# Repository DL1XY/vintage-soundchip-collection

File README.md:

# Vintage Soundchip Collection

> Parts of this README were generated using AI.

My personal collection of vintage sound and speech chips from the 1970s to the early 1990s. Browse by part number for chip photos, datasheets, service manuals, and notes for building your own circuits. Each chip page also has a short story about where it showed up or what people got it to do.

## Circuit projects

- **UM6526P1 PAL TIA / ESP32 (Rev. A)**. Prototype design with structural checks. [Schematic PDF](CO10444_TIA/TIA_UM6526P1_Schematic_RevA_EN.pdf) · [Project files and verification notes](CO10444_TIA/TIA_UM6526P1_RevA_EN/README.md)
- **POKEY / ESP32 (Rev. A)**. Document-reviewed prototype design. [Schematic PDF](CO12294_POKEY/POKEY_ESP32_RevA_EN/POKEY_ESP32_Schematic_RevA_EN.pdf) · [Project files and verification notes](CO12294_POKEY/POKEY_ESP32_RevA_EN/README.md)

Both projects still need hardware testing.

## Chip catalog

| IC            | Company               | Type | Image         | KiCAD Symbol  |
| ------------- | --------------------- | ---- | ------------- | ------------- |
| [8245](8245)  | Intel                 | Multifunction (video/audio) |  | :triangular_ruler: |
| [AY-3-8910](AY-3-8910)  | General Instrument | PSG |  | :triangular_ruler: |
| [CDP1869](CDP1869) | RCA | Multifunction (video/audio) |  | :triangular_ruler: |
| [CO10444 TIA](CO10444_TIA) | Atari | Multifunction (video/audio) | <br>UM6526 TIA variant | :triangular_ruler: |
| [CO12294 POKEY](CO12294_POKEY) | Atari | Multifunction (I/O and audio) |  | :triangular_ruler: |
| [MEA8000](MEA8000) | TMPI | Speech synthesis |  | :triangular_ruler: |
| [MEB2636](MEB2636) | Signetics/Philips | Multifunction (video/audio) |  | :triangular_ruler: |
| [MM54104 DIGITALKER](MM54104) | Mozer| Speech synthesis |  | :triangular_ruler:  |
| [MN6221](MN6221) | Panasonic| Melody generator | <br>MN6221AA | :triangular_ruler:  |
| [MOS6560 VIC](MOS6560_VIC) | Commodore| Multifunction (video/audio) | <br>MOS6561 PAL VIC | :triangular_ruler: |
| [MOS6581 SID](MOS6581_SID) | Commodore| Subtractive synthesis |  | :triangular_ruler: |
| [MOS8360 TED](MOS8360_TED) | Commodore| Multifunction (video/audio) |  | :triangular_ruler: |
| [MOS8364 PAULA](MOS8364_PAULA) | Commodore| Multifunction (PCM audio and I/O) |  | :triangular_ruler: |
| [MSM5205](MSM5205) | OKI| ADPCM | <br>M5205 | :triangular_ruler:  |
| [MSM5218](MSM5218) | OKI| ADPCM | <br>M5218 | :triangular_ruler:  |
| [PCF8200](PCF8200) | Philips| Speech synthesis |  | :triangular_ruler:  |
| [SC-01](SC-01) | Votrax| Speech synthesis | <br>SC-01-A | No symbol |
| [SAA1099](SAA1099) | Philips| PSG |  | :triangular_ruler: |
| [SN76477](SN76477) | Texas Instruments| Sound effects generator |  | :triangular_ruler: |
| [SN76488](SN76488) | Texas Instruments| Sound effects generator |  | :triangular_ruler: |
| [SN76489](SN76489) | Texas Instruments| PSG | <br>SN76489AN | :triangular_ruler: |
| [SP0250](SP0250) | General Instrument| Speech synthesis |  | :triangular_ruler: |
| [SP0256](SP0256) | General Instrument| Speech synthesis | <br>SP0256A | :triangular_ruler: |
| [SP1000](SP1000) | General Instrument| Speech synthesis and recognition |  | :triangular_ruler: |
| [TMS3477](TMS3477) | Texas Instruments| Voice recording/playback |  | :triangular_ruler: |
| [TMS5110](TMS5110) | Texas Instruments| Speech synthesis |  | :triangular_ruler: |
| [TMS5200](TMS5200) | Texas Instruments| Speech synthesis |  | :triangular_ruler: |
| [TMS5220](TMS5220) | Texas Instruments| Speech synthesis |  | :triangular_ruler: |
| [UAA1003](UAA1003) | ITT| Speech synthesis |  | :triangular_ruler: |
| [VRC6](VRC6) | Konami| Multifunction (mapper/audio) | No image |No symbol |
| [VLM5030](VLM5030) | Sanyo| Speech synthesis |  | :triangular_ruler: |
| [YM2151](YM2151) | Yamaha| FM synthesis |  | :triangular_ruler: |
| [YM2203](YM2203) | Yamaha| FM synthesis + PSG |  | :triangular_ruler: |
| [YM2413](YM2413) | Yamaha| FM synthesis |  | :triangular_ruler: |
| [YM2610](YM2610) | Yamaha| FM synthesis + PSG + ADPCM |  | :triangular_ruler: |
| [YM3438](YM3438) | Yamaha| FM synthesis |  | :triangular_ruler: |
| [YM3812](YM3812) | Yamaha| FM synthesis |  | :triangular_ruler: |

PSG = programmable sound generator. Multifunction chips provide audio alongside other hardware functions.

## KiCAD Symbols

[8_bit_soundchips.kicad_sym](8_bit_soundchips.kicad_sym) contains KiCAD symbols of chips marked with :triangular_ruler:

Tested with KiCAD 10.x

## Wishlist

+ Ricoh 2A03/2A07
+ Sunsoft 5B
+ misc Harris 
+ misc Nintendo (MMC5, 2C33, ...)
+ misc Yamaha
+ misc Konami (RC,...)
+ misc Namco (WSG, 163, ...)
+ OKI MSM5232
+ OKI 6295

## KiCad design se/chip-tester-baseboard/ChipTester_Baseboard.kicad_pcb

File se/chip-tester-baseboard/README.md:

# USB-C Sound Chip Tester Baseboard · Rev A

Open [ChipTester_Baseboard.kicad_pro](ChipTester_Baseboard.kicad_pro) in KiCad 8 or newer. The project has five schematic sheets and an 82 × 69 mm four-layer PCB. Keep the schematic sheets, library tables, symbol library and `Baseboard.pretty` folder together. The PCB includes routed copper and an In1.Cu ground zone. Press **B** in the PCB Editor to fill the zone before running DRC.

| Sheet | Circuit |
| --- | --- |
| USB-C | GCT USB4105 receptacle, separate CC pull-downs, flow-through USBLC6 data ESD clamp and 27 Ω series resistors |
| Power | AP2112K 3.3 V supply and firmware-enabled TPS2553 adapter supply. Pull-down on the enable input defaults the adapter supply off. |
| RP2350B | QSPI flash, 12 MHz crystal, 1.1 V core buck, BOOTSEL, reset and SWD |
| Adapter | One keyed 2×20 IDC connector with the pin numbering from the [architecture](../chip-tester-design.md). Disconnect USB to swap adapters. |
| Audio | Independent, AC-coupled L/MONO and R line outputs. Fixed unity-gain buffers and default mute. Use line inputs of 10 kΩ or higher. |

The layout uses an internal ground plane and places the audio buffers, analog switch and filter components next to the output jacks. Two buffered controls drive the analog switch at its 5 V logic levels. The adapter supplies the chip-specific signal conditioning and output level. A mono adapter connects to `AUDIO_L`. Leave the right channel muted in firmware.

## RP2350B firmware pin assignments

| GPIO | Signal |
| --- | --- |
| GP4–GP11 | D0–D7, contiguous for PIO |
| GP12–GP17 | A0–A5 |
| GP18–GP21 | CTRL0–CTRL3 |
| GP22, GP23 | CLK_OUT, RESET_N |
| GP24, GP25 | ID_SDA, ID_SCL |
| GP26, GP27 | BUS_EN, DATA_DIR |
| GP28, GP29–GP31 | READY_IRQ, AUX0–AUX2 |
| GP32, GP33 | ADAPTER_EN, ADAPTER_FAULT_N |
| GP34, GP35 | AUDIO_L_EN, AUDIO_R_EN |

Adapter ID runs on the always-on 3.3 V pin and dedicated ID bus. Keep the adapter's 5 V supply and bus drivers disabled through USB configuration and profile identification. On suspend or fault, mute the outputs, disable the bus and remove adapter power. This project contains the hardware. USB CDC commands and chip profiles require firmware.

## Prototype verification

The schematic and PCB were checked for footprint linkage, pin-to-net agreement and routed connectivity. KiCad ERC, filled-zone DRC and native import remain to be run. Before sending Gerbers, review the USB pair and chosen PCB stack-up, ground fill, component land patterns and fab limits. The layout uses 0.40 mm signal vias with 0.20 mm finished drills and 0.12 mm minimum design clearance. The RP2350B exposed pad requires reflow assembly. Review stencil apertures and exposed-pad via treatment with the board supplier.

On initial power-up, measure protected VBUS, 3.3 V, 1.1 V and the audio midpoint. Check USB enumeration and BOOTSEL with the adapter supply off, then verify the TPS2553 current limit with a dummy load. The 82.5 kΩ limit resistor is provisional pending measurements of baseboard current, adapter inrush and total USB current. Measure audio noise, output level and power-transition transients before using the line outputs for comparisons.

The [batch workbook](../chip-tester-bom/Chip%20Tester%20BOM.xlsx) is the earlier cost estimate. Extract the baseboard purchase list from the schematic. This revision adds an SN74AHCT125 buffer and uses 0402 passives near the RP2350B and analog switch.

## Design references

- [Raspberry Pi RP2350 hardware design guide](https://pip-assets.raspberrypi.com/categories/1214-rp2350/documents/RP-008280-DS-1-hardware-design-with-rp2350.pdf)
- [GCT USB4105 mechanical drawing](https://gct.co/files/drawings/usb4105.pdf)
- [ST USBLC6-2SC6 datasheet](https://www.st.com/resource/en/datasheet/usblc6-2sc6.pdf)
- [TI TPS2553 datasheet](https://www.ti.com/lit/ds/symlink/tps2553.pdf)
- [TI TS5A23157 datasheet](https://www.ti.com/lit/ds/symlink/ts5a23157.pdf)
- [Same Sky SJ1-3523N mechanical drawing](https://www.sameskydevices.com/product/resource/sj1-352xn.pdf)

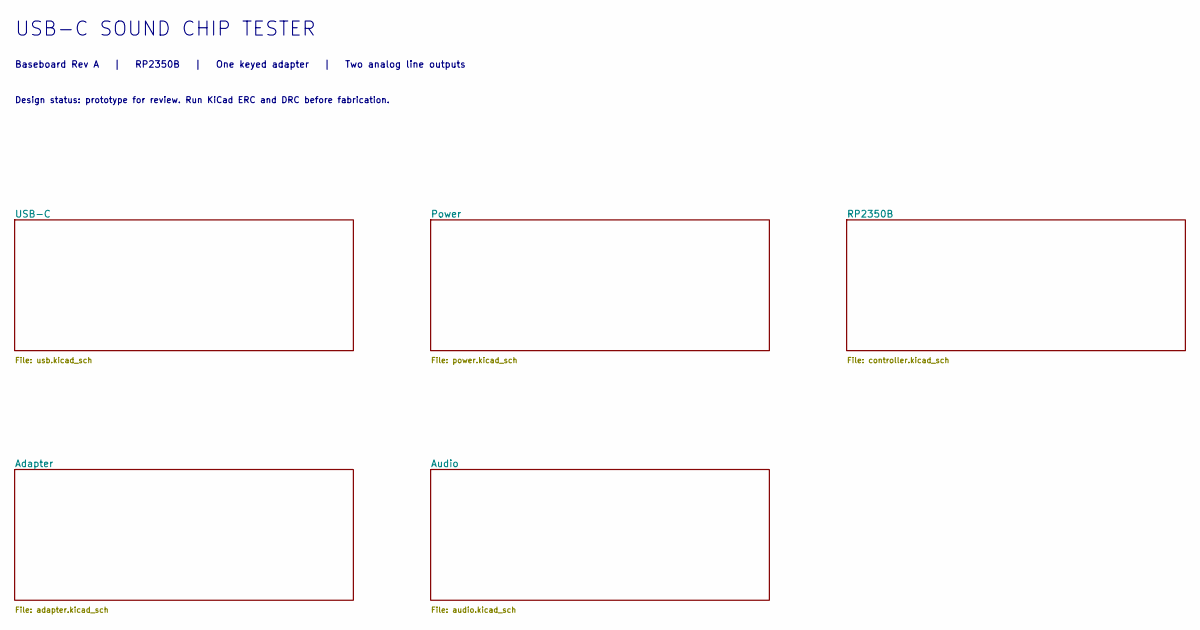
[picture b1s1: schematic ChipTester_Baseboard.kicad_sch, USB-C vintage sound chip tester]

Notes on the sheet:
USB-C SOUND CHIP TESTER
Design status: prototype for review. Run KiCad ERC and DRC before fabrication.
Baseboard Rev A | RP2350B | One keyed adapter | Two analog line outputs

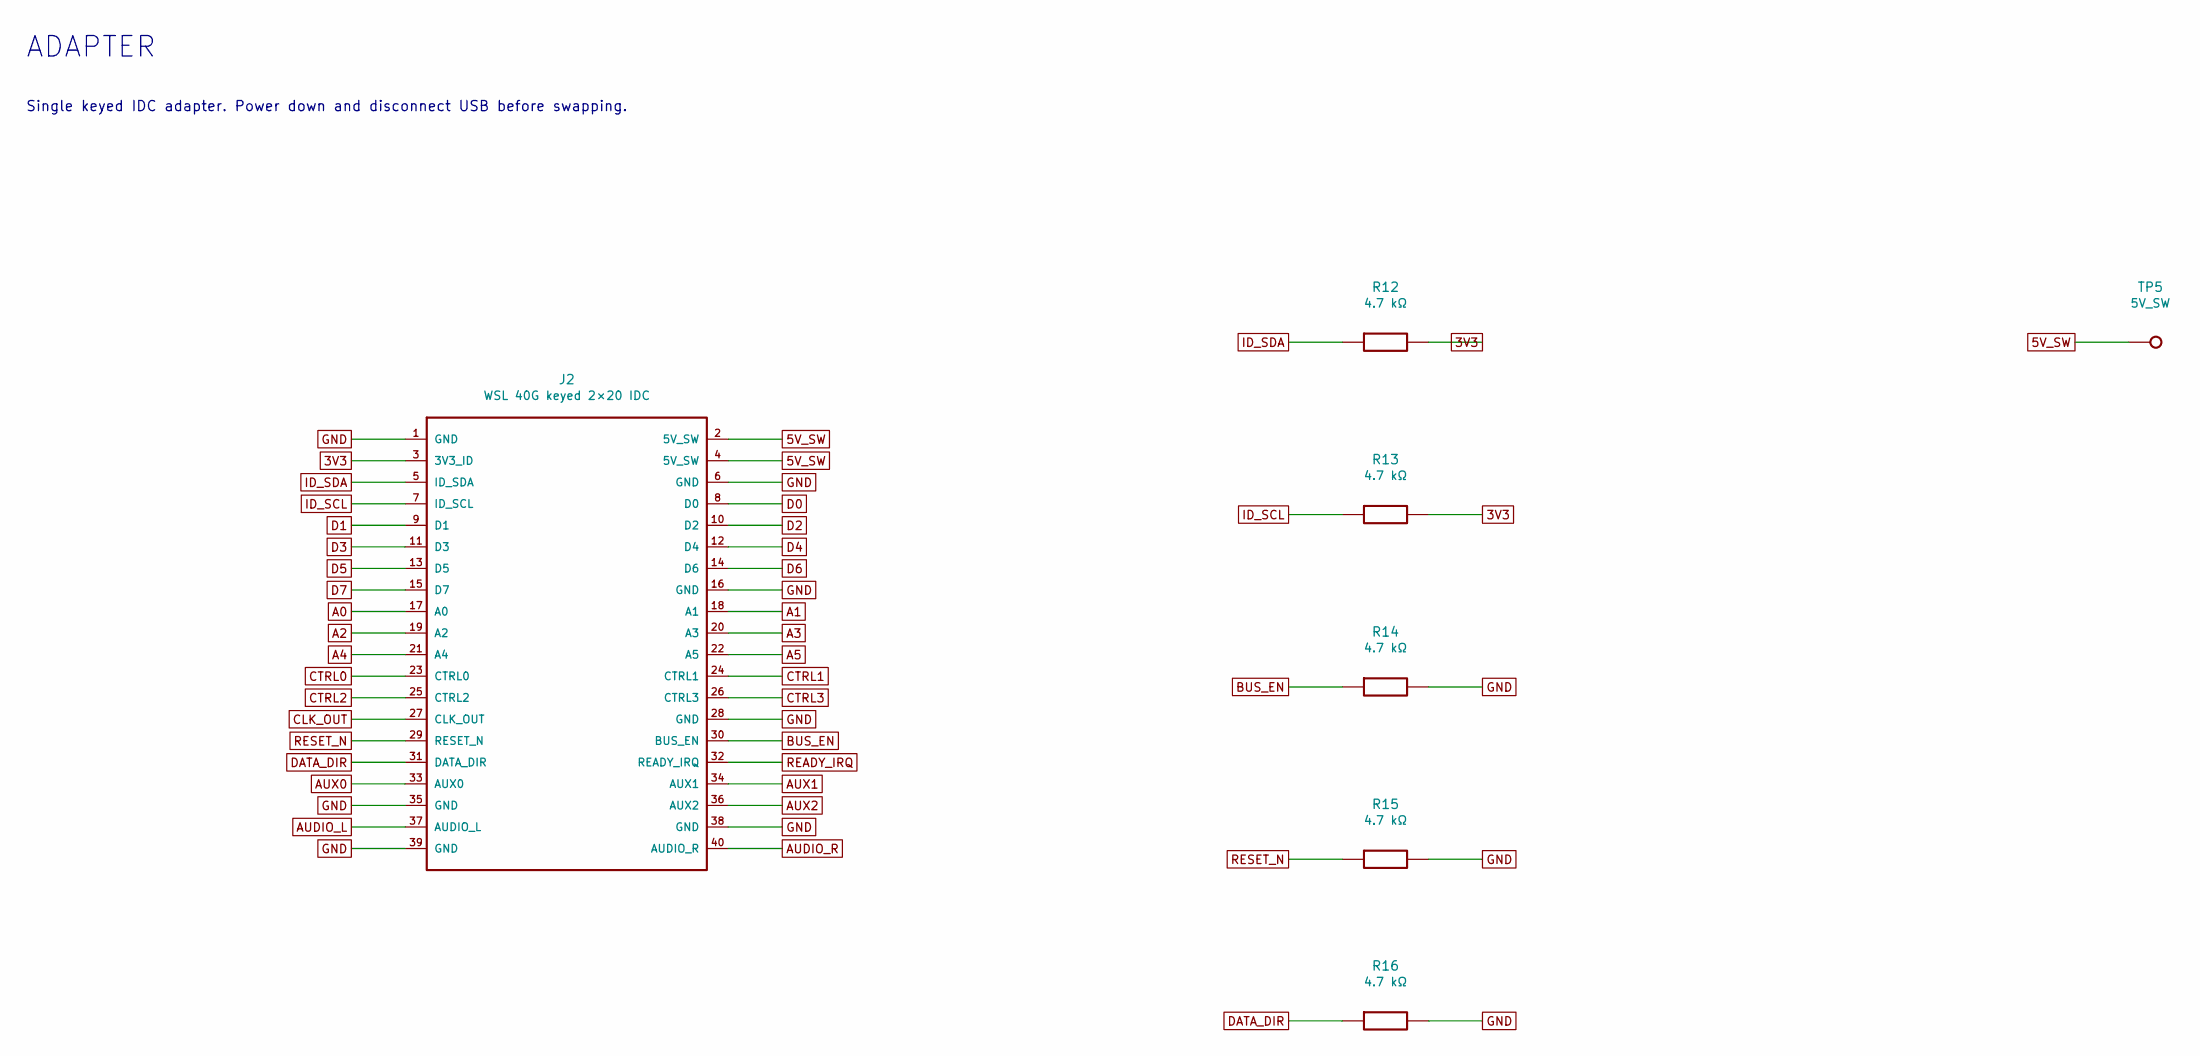
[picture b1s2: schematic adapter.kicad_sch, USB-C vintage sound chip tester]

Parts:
J2: WSL 40G keyed 2×20 IDC; IDC_2x20
R12, R13, R14, R15, R16: 4.7 kΩ; R_0805
TP5: 5V_SW; TestPoint_1mm

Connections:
3V3: J2.3 (3V3_ID), R12.2, R13.2; also elsewhere on the board
5V_SW: J2.2 (5V_SW), J2.4 (5V_SW), TP5.1; also elsewhere on the board
A0: J2.17 (A0); also elsewhere on the board
A1: J2.18 (A1); also elsewhere on the board
A2: J2.19 (A2); also elsewhere on the board
A3: J2.20 (A3); also elsewhere on the board
A4: J2.21 (A4); also elsewhere on the board
A5: J2.22 (A5); also elsewhere on the board
AUDIO_L: J2.37 (AUDIO_L); also elsewhere on the board
AUDIO_R: J2.40 (AUDIO_R); also elsewhere on the board
AUX0: J2.33 (AUX0); also elsewhere on the board
AUX1: J2.34 (AUX1); also elsewhere on the board
AUX2: J2.36 (AUX2); also elsewhere on the board
BUS_EN: J2.30 (BUS_EN), R14.1; also elsewhere on the board
CLK_OUT: J2.27 (CLK_OUT); also elsewhere on the board
CTRL0: J2.23 (CTRL0); also elsewhere on the board
CTRL1: J2.24 (CTRL1); also elsewhere on the board
CTRL2: J2.25 (CTRL2); also elsewhere on the board
CTRL3: J2.26 (CTRL3); also elsewhere on the board
D0: J2.8 (D0); also elsewhere on the board
D1: J2.9 (D1); also elsewhere on the board
D2: J2.10 (D2); also elsewhere on the board
D3: J2.11 (D3); also elsewhere on the board
D4: J2.12 (D4); also elsewhere on the board
D5: J2.13 (D5); also elsewhere on the board
D6: J2.14 (D6); also elsewhere on the board
D7: J2.15 (D7); also elsewhere on the board
DATA_DIR: J2.31 (DATA_DIR), R16.1; also elsewhere on the board
GND: J2.1 (GND), J2.6 (GND), J2.16 (GND), J2.28 (GND), J2.35 (GND), J2.38 (GND), J2.39 (GND), R14.2, R15.2, R16.2; also elsewhere on the board
ID_SCL: J2.7 (ID_SCL), R13.1; also elsewhere on the board
ID_SDA: J2.5 (ID_SDA), R12.1; also elsewhere on the board
READY_IRQ: J2.32 (READY_IRQ); also elsewhere on the board
RESET_N: J2.29 (RESET_N), R15.1; also elsewhere on the board

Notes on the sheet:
ADAPTER
Single keyed IDC adapter. Power down and disconnect USB before swapping.

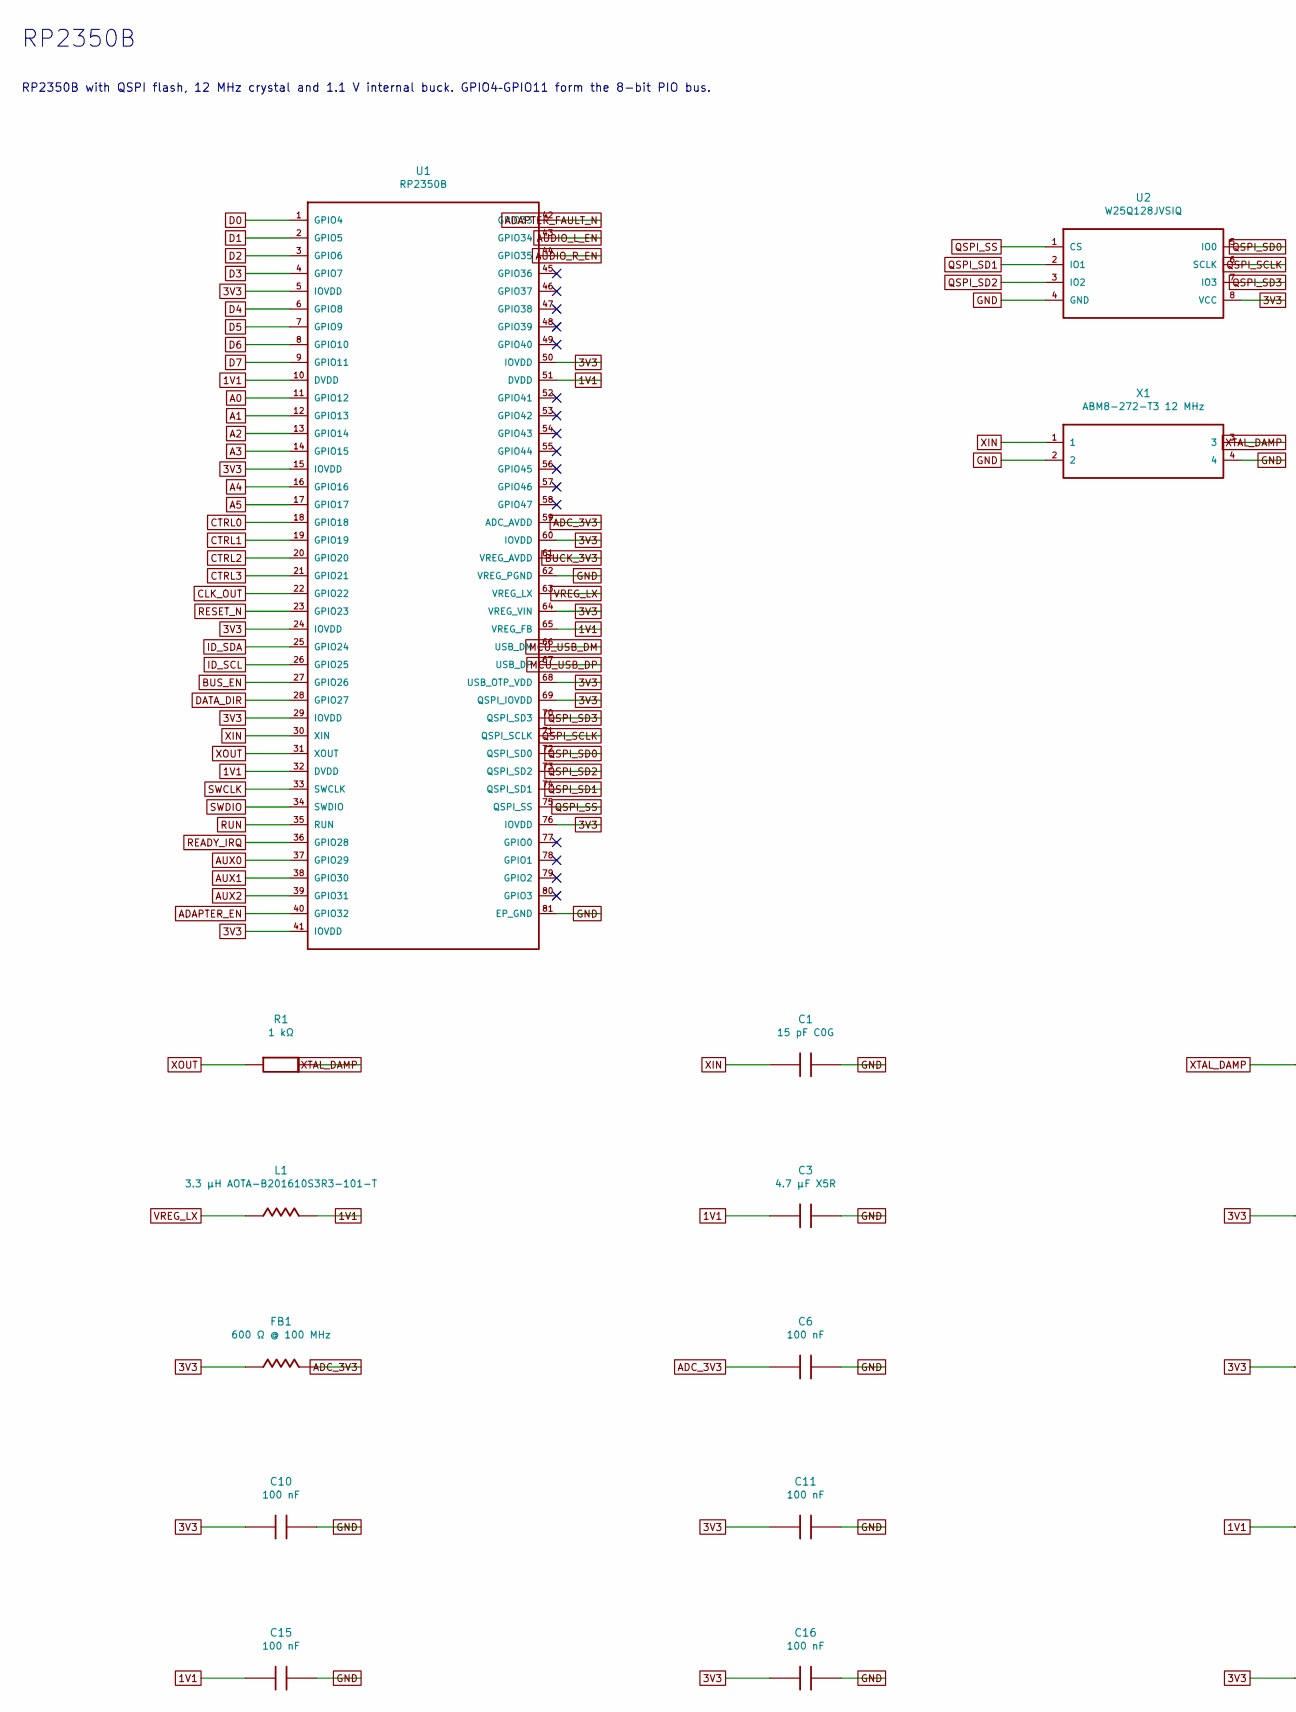
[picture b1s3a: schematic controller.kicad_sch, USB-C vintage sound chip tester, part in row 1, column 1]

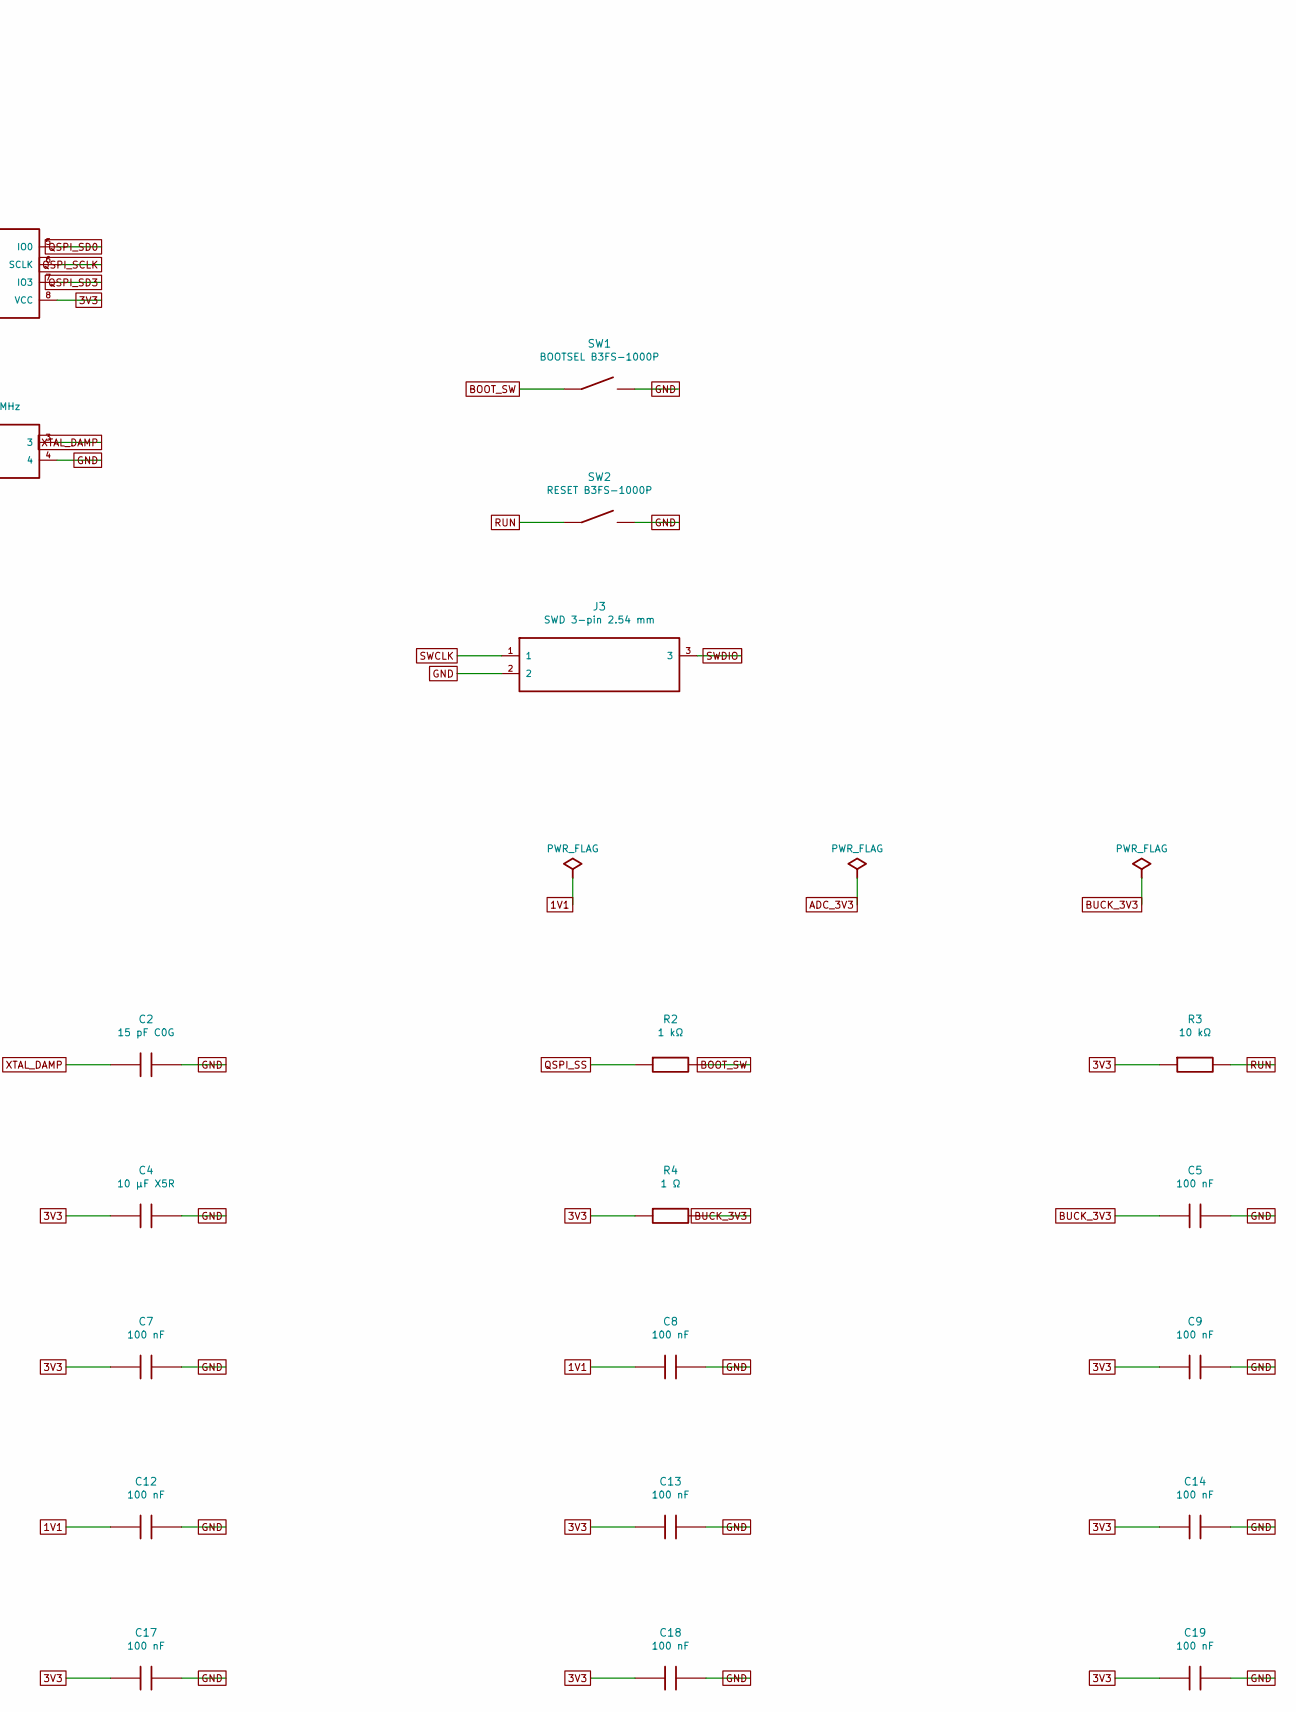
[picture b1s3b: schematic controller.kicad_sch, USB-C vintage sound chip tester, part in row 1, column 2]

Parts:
C1, C2: 15 pF C0G; C_0402
C3: 4.7 µF X5R; C_0603
C4: 10 µF X5R; C_0603_R90
C5, C6, C7, C8, C9, C11, C12, C13, C14, C15, C16, C18, C19: 100 nF; C_0402
C10, C17: 100 nF; C_0402_R90
FB1: 600 Ω @ 100 MHz; FB_0603
J3: SWD 3-pin 2.54 mm; Header_1x03
L1: 3.3 µH AOTA-B201610S3R3-101-T; L_L2016
R1, R2: 1 kΩ; R_0402
R3: 10 kΩ; R_0805
R4: 1 Ω; R_0402
SW1: BOOTSEL B3FS-1000P; B3FS_1000P
SW2: RESET B3FS-1000P; B3FS_1000P
U1: RP2350B; QFN80_RP2350B
U2: W25Q128JVSIQ; SOIC8_5.3mm_R90
X1: ABM8-272-T3 12 MHz; Crystal_3225

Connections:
1V1: C3.1, C8.1, C12.1, C15.1, L1.2, U1.10 (DVDD), U1.32 (DVDD), U1.51 (DVDD), U1.65 (VREG_FB); also elsewhere on the board
3V3: C4.1, C7.1, C9.1, C10.1, C11.1, C13.1, C14.1, C16.1, C17.1, C18.1, C19.1, FB1.1, R3.1, R4.1, U1.5 (IOVDD), U1.15 (IOVDD), U1.24 (IOVDD), U1.29 (IOVDD), U1.41 (IOVDD), U1.50 (IOVDD), U1.60 (IOVDD), U1.64 (VREG_VIN), U1.68 (USB_OTP_VDD), U1.69 (QSPI_IOVDD), U1.76 (IOVDD), U2.8 (VCC); also elsewhere on the board
A0: U1.11 (GPIO12); also elsewhere on the board
A1: U1.12 (GPIO13); also elsewhere on the board
A2: U1.13 (GPIO14); also elsewhere on the board
A3: U1.14 (GPIO15); also elsewhere on the board
A4: U1.16 (GPIO16); also elsewhere on the board
A5: U1.17 (GPIO17); also elsewhere on the board
ADAPTER_EN: U1.40 (GPIO32); also elsewhere on the board
ADAPTER_FAULT_N: U1.42 (GPIO33); also elsewhere on the board
ADC_3V3: C6.1, FB1.2, U1.59 (ADC_AVDD)
AUDIO_L_EN: U1.43 (GPIO34); also elsewhere on the board
AUDIO_R_EN: U1.44 (GPIO35); also elsewhere on the board
AUX0: U1.37 (GPIO29); also elsewhere on the board
AUX1: U1.38 (GPIO30); also elsewhere on the board
AUX2: U1.39 (GPIO31); also elsewhere on the board
BOOT_SW: R2.2, SW1.1
BUCK_3V3: C5.1, R4.2, U1.61 (VREG_AVDD)
BUS_EN: U1.27 (GPIO26); also elsewhere on the board
CLK_OUT: U1.22 (GPIO22); also elsewhere on the board
CTRL0: U1.18 (GPIO18); also elsewhere on the board
CTRL1: U1.19 (GPIO19); also elsewhere on the board
CTRL2: U1.20 (GPIO20); also elsewhere on the board
CTRL3: U1.21 (GPIO21); also elsewhere on the board
D0: U1.1 (GPIO4); also elsewhere on the board
D1: U1.2 (GPIO5); also elsewhere on the board
D2: U1.3 (GPIO6); also elsewhere on the board
D3: U1.4 (GPIO7); also elsewhere on the board
D4: U1.6 (GPIO8); also elsewhere on the board
D5: U1.7 (GPIO9); also elsewhere on the board
D6: U1.8 (GPIO10); also elsewhere on the board
D7: U1.9 (GPIO11); also elsewhere on the board
DATA_DIR: U1.28 (GPIO27); also elsewhere on the board
GND: C1.2, C2.2, C3.2, C4.2, C5.2, C6.2, C7.2, C8.2, C9.2, C10.2, C11.2, C12.2, C13.2, C14.2, C15.2, C16.2, C17.2, C18.2, C19.2, J3.2, SW1.2, SW2.2, U1.62 (VREG_PGND), U1.81 (EP_GND), U2.4 (GND), X1.2, X1.4; also elsewhere on the board
ID_SCL: U1.26 (GPIO25); also elsewhere on the board
ID_SDA: U1.25 (GPIO24); also elsewhere on the board
MCU_USB_DM: U1.66 (USB_DM); also elsewhere on the board
MCU_USB_DP: U1.67 (USB_DP); also elsewhere on the board
QSPI_SCLK: U1.71 (QSPI_SCLK), U2.6 (SCLK)
QSPI_SD0: U1.72 (QSPI_SD0), U2.5 (IO0)
QSPI_SD1: U1.74 (QSPI_SD1), U2.2 (IO1)
QSPI_SD2: U1.73 (QSPI_SD2), U2.3 (IO2)
QSPI_SD3: U1.70 (QSPI_SD3), U2.7 (IO3)
QSPI_SS: R2.1, U1.75 (QSPI_SS), U2.1 (CS)
READY_IRQ: U1.36 (GPIO28); also elsewhere on the board
RESET_N: U1.23 (GPIO23); also elsewhere on the board
RUN: R3.2, SW2.1, U1.35 (RUN)
SWCLK: J3.1, U1.33 (SWCLK)
SWDIO: J3.3, U1.34 (SWDIO)
VREG_LX: L1.1, U1.63 (VREG_LX)
XIN: C1.1, U1.30 (XIN), X1.1
XOUT: R1.1, U1.31 (XOUT)
XTAL_DAMP: C2.1, R1.2, X1.3

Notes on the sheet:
RP2350B with QSPI flash, 12 MHz crystal and 1.1 V internal buck. GPIO4–GPIO11 form the 8-bit PIO bus.
RP2350B

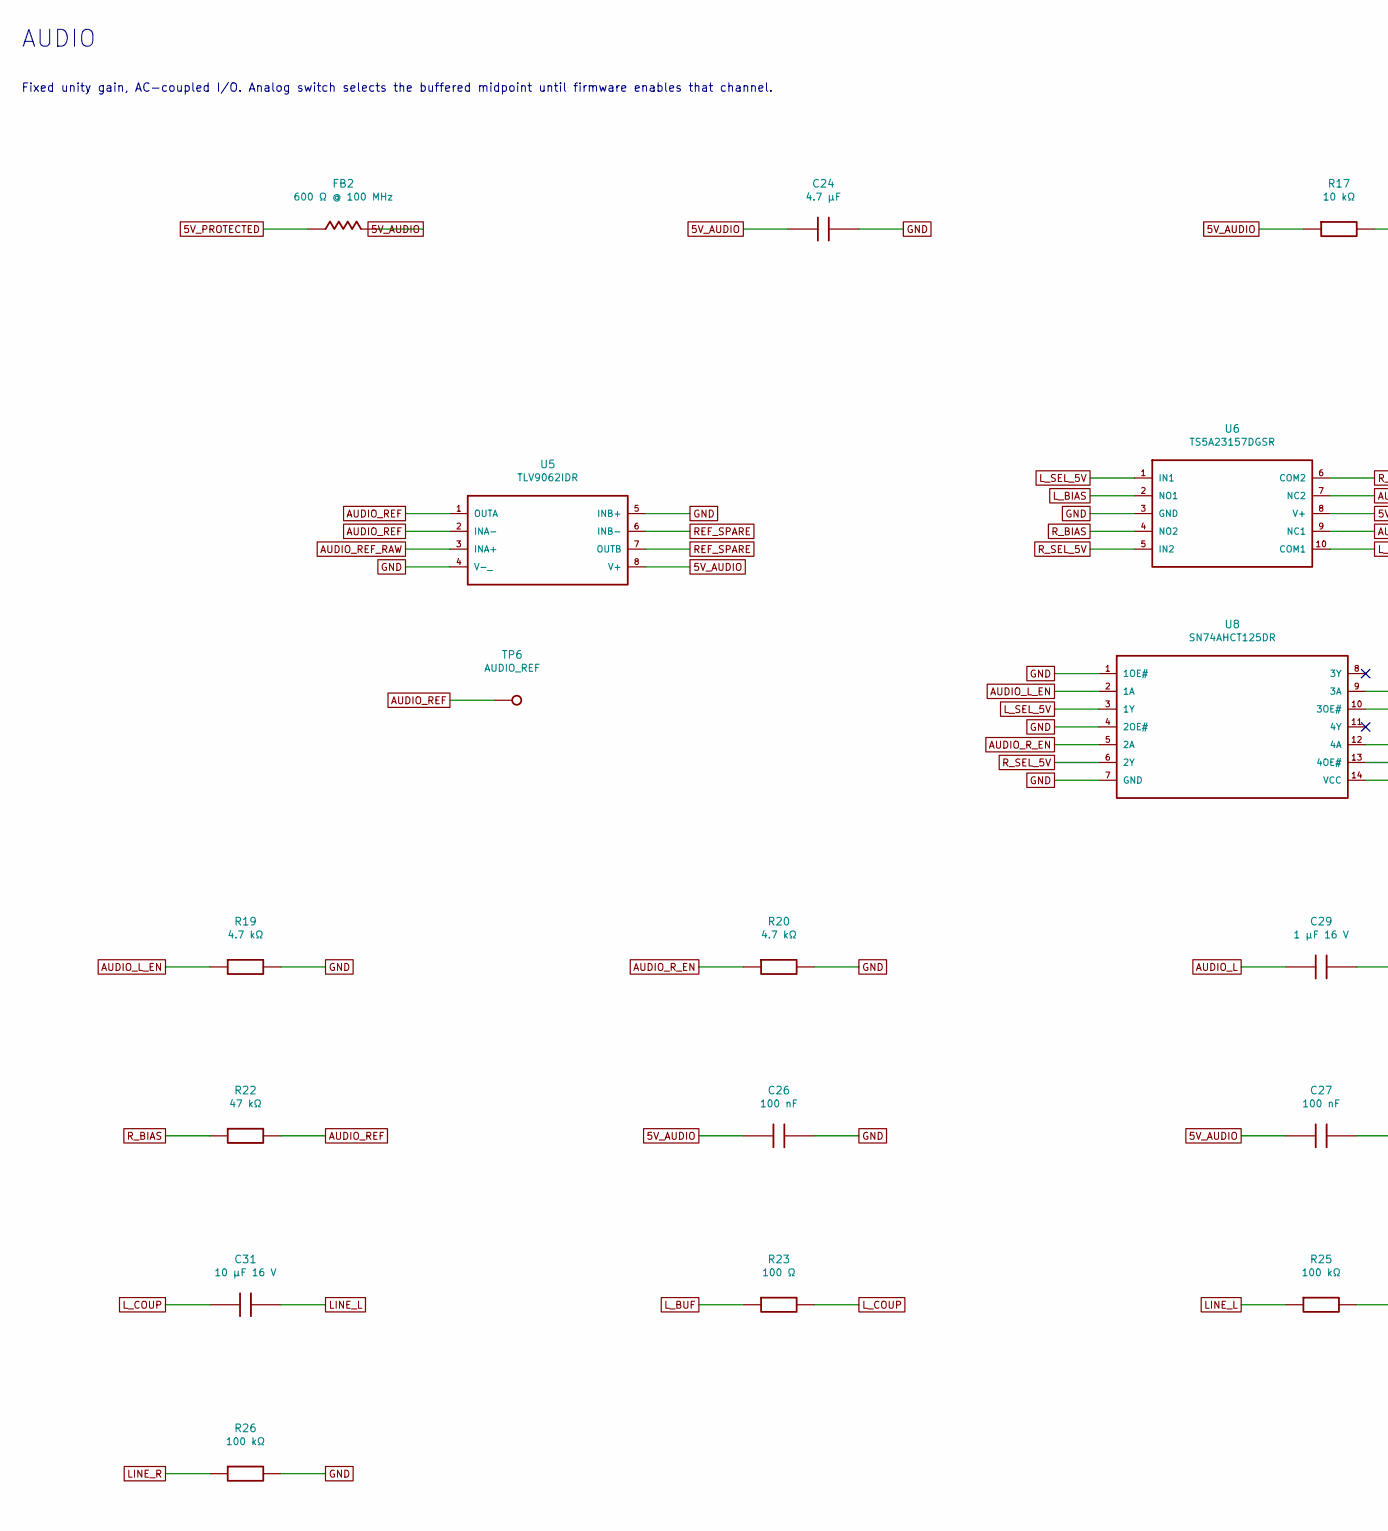
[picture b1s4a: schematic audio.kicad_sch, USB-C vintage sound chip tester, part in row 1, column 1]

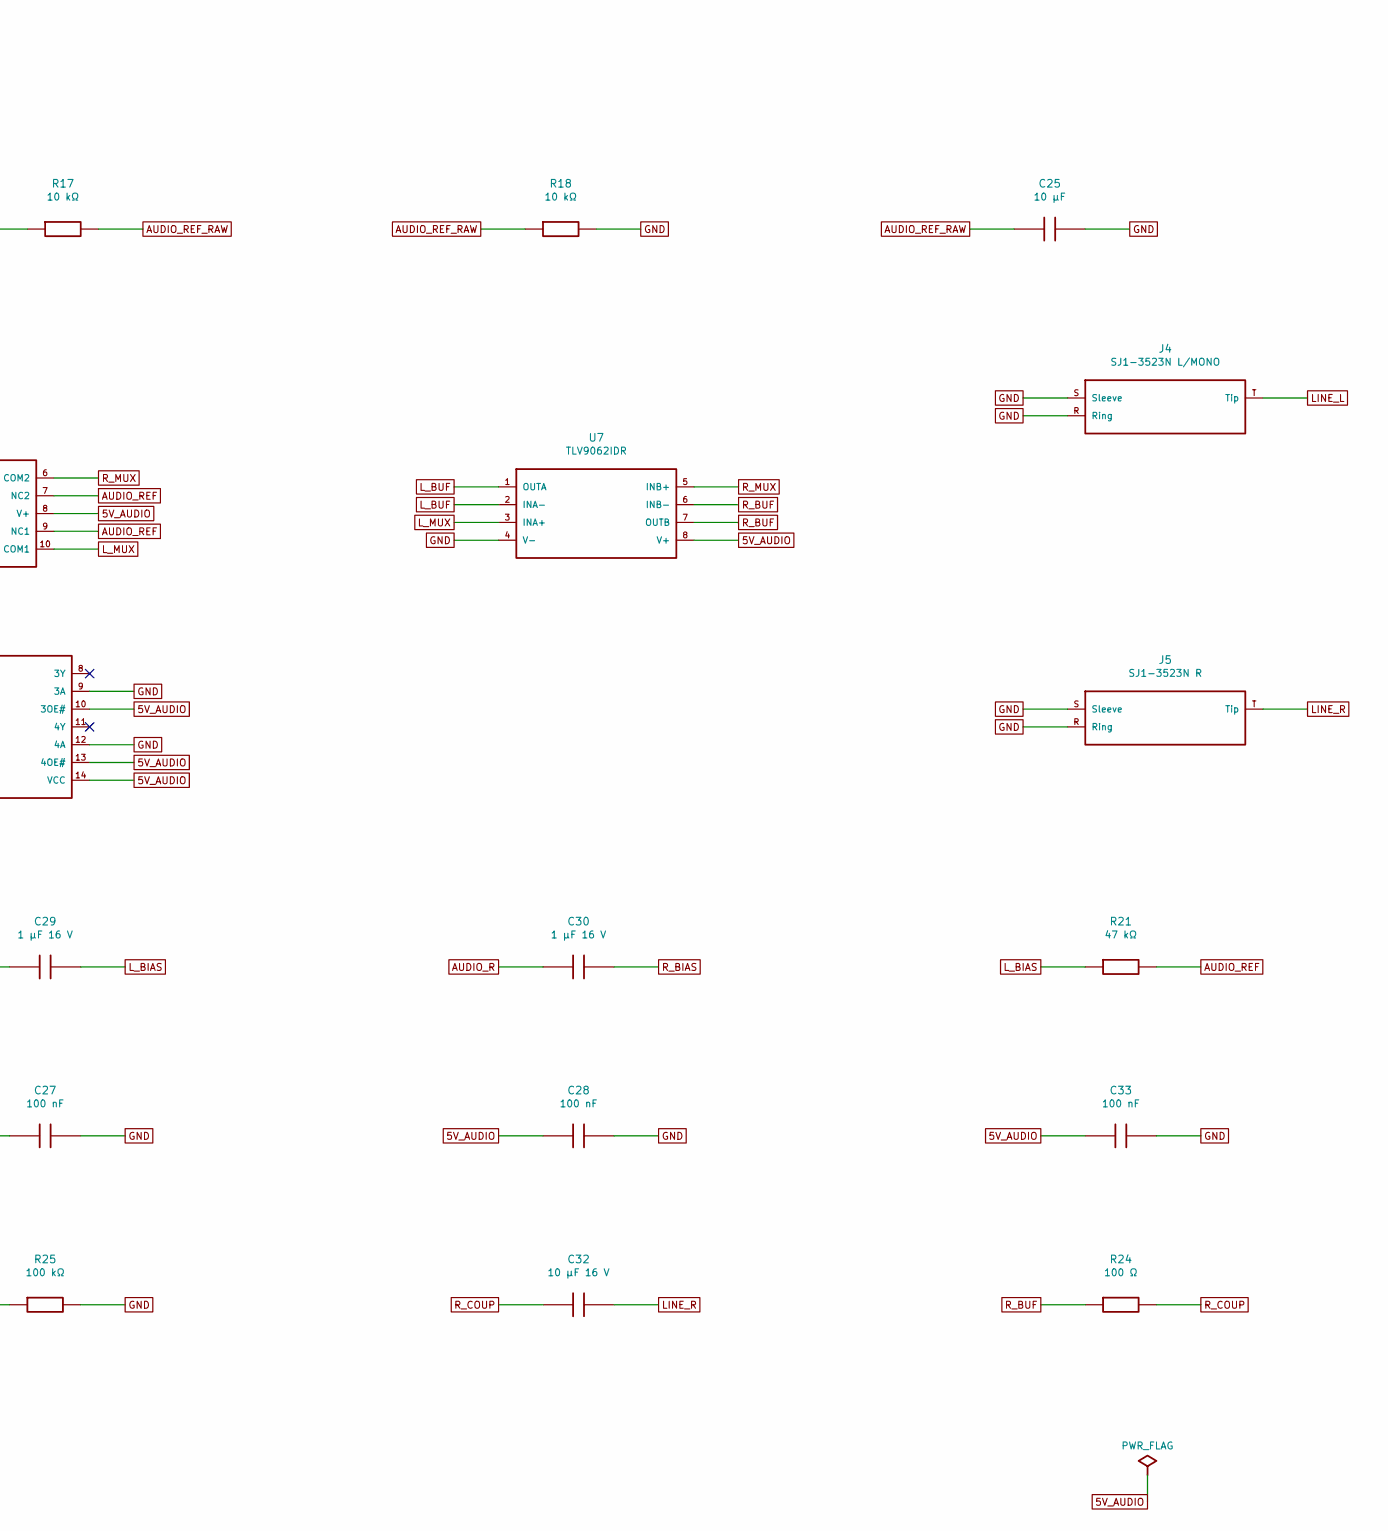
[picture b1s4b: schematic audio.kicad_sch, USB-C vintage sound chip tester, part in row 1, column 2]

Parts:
C24: 4.7 µF; C_0805
C25: 10 µF; C_0805
C26, C27, C28, C33: 100 nF; C_0402
C29, C30: 1 µF 16 V; C_0603_R90
C31, C32: 10 µF 16 V; C_1206
FB2: 600 Ω @ 100 MHz; FB_0805
J4: SJ1-3523N L/MONO; SJ1_3523N
J5: SJ1-3523N R; SJ1_3523N
R17, R18: 10 kΩ; R_0805
R19, R20: 4.7 kΩ; R_0603
R21, R22: 47 kΩ; R_0603_R90
R23: 100 Ω; R_0805
R24: 100 Ω; R_0805_R90
R25, R26: 100 kΩ; R_0603
TP6: AUDIO_REF; TestPoint_1mm
U5, U7: TLV9062IDR; SOIC8
U6: TS5A23157DGSR; VSSOP10
U8: SN74AHCT125DR; SOIC14

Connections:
5V_AUDIO: C24.1, C26.1, C27.1, C28.1, C33.1, FB2.2, R17.1, U5.8 (V+), U6.8 (V+), U7.8 (V+), U8.10 (3OE#), U8.13 (4OE#), U8.14 (VCC)
5V_PROTECTED: FB2.1; also elsewhere on the board
AUDIO_L: C29.1; also elsewhere on the board
AUDIO_L_EN: R19.1, U8.2 (1A); also elsewhere on the board
AUDIO_R: C30.1; also elsewhere on the board
AUDIO_REF: R21.2, R22.2, TP6.1, U5.1 (OUTA), U5.2 (INA-), U6.7 (NC2), U6.9 (NC1)
AUDIO_REF_RAW: C25.1, R17.2, R18.1, U5.3 (INA+)
AUDIO_R_EN: R20.1, U8.5 (2A); also elsewhere on the board
GND: C24.2, C25.2, C26.2, C27.2, C28.2, C33.2, J4.R (Ring), J4.S (Sleeve), J5.R (Ring), J5.S (Sleeve), R18.2, R19.2, R20.2, R25.2, R26.2, U5.4 (V-_), U5.5 (INB+), U6.3 (GND), U7.4 (V-), U8.1 (1OE#), U8.4 (2OE#), U8.7 (GND), U8.9 (3A), U8.12 (4A); also elsewhere on the board
LINE_L: C31.2, J4.T (Tip), R25.1
LINE_R: C32.2, J5.T (Tip), R26.1
L_BIAS: C29.2, R21.1, U6.2 (NO1)
L_BUF: R23.1, U7.1 (OUTA), U7.2 (INA-)
L_COUP: C31.1, R23.2
L_MUX: U6.10 (COM1), U7.3 (INA+)
L_SEL_5V: U6.1 (IN1), U8.3 (1Y)
REF_SPARE: U5.6 (INB-), U5.7 (OUTB)
R_BIAS: C30.2, R22.1, U6.4 (NO2)
R_BUF: R24.1, U7.6 (INB-), U7.7 (OUTB)
R_COUP: C32.1, R24.2
R_MUX: U6.6 (COM2), U7.5 (INB+)
R_SEL_5V: U6.5 (IN2), U8.6 (2Y)

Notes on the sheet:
AUDIO
Fixed unity gain, AC-coupled I/O. Analog switch selects the buffered midpoint until firmware enables that channel.

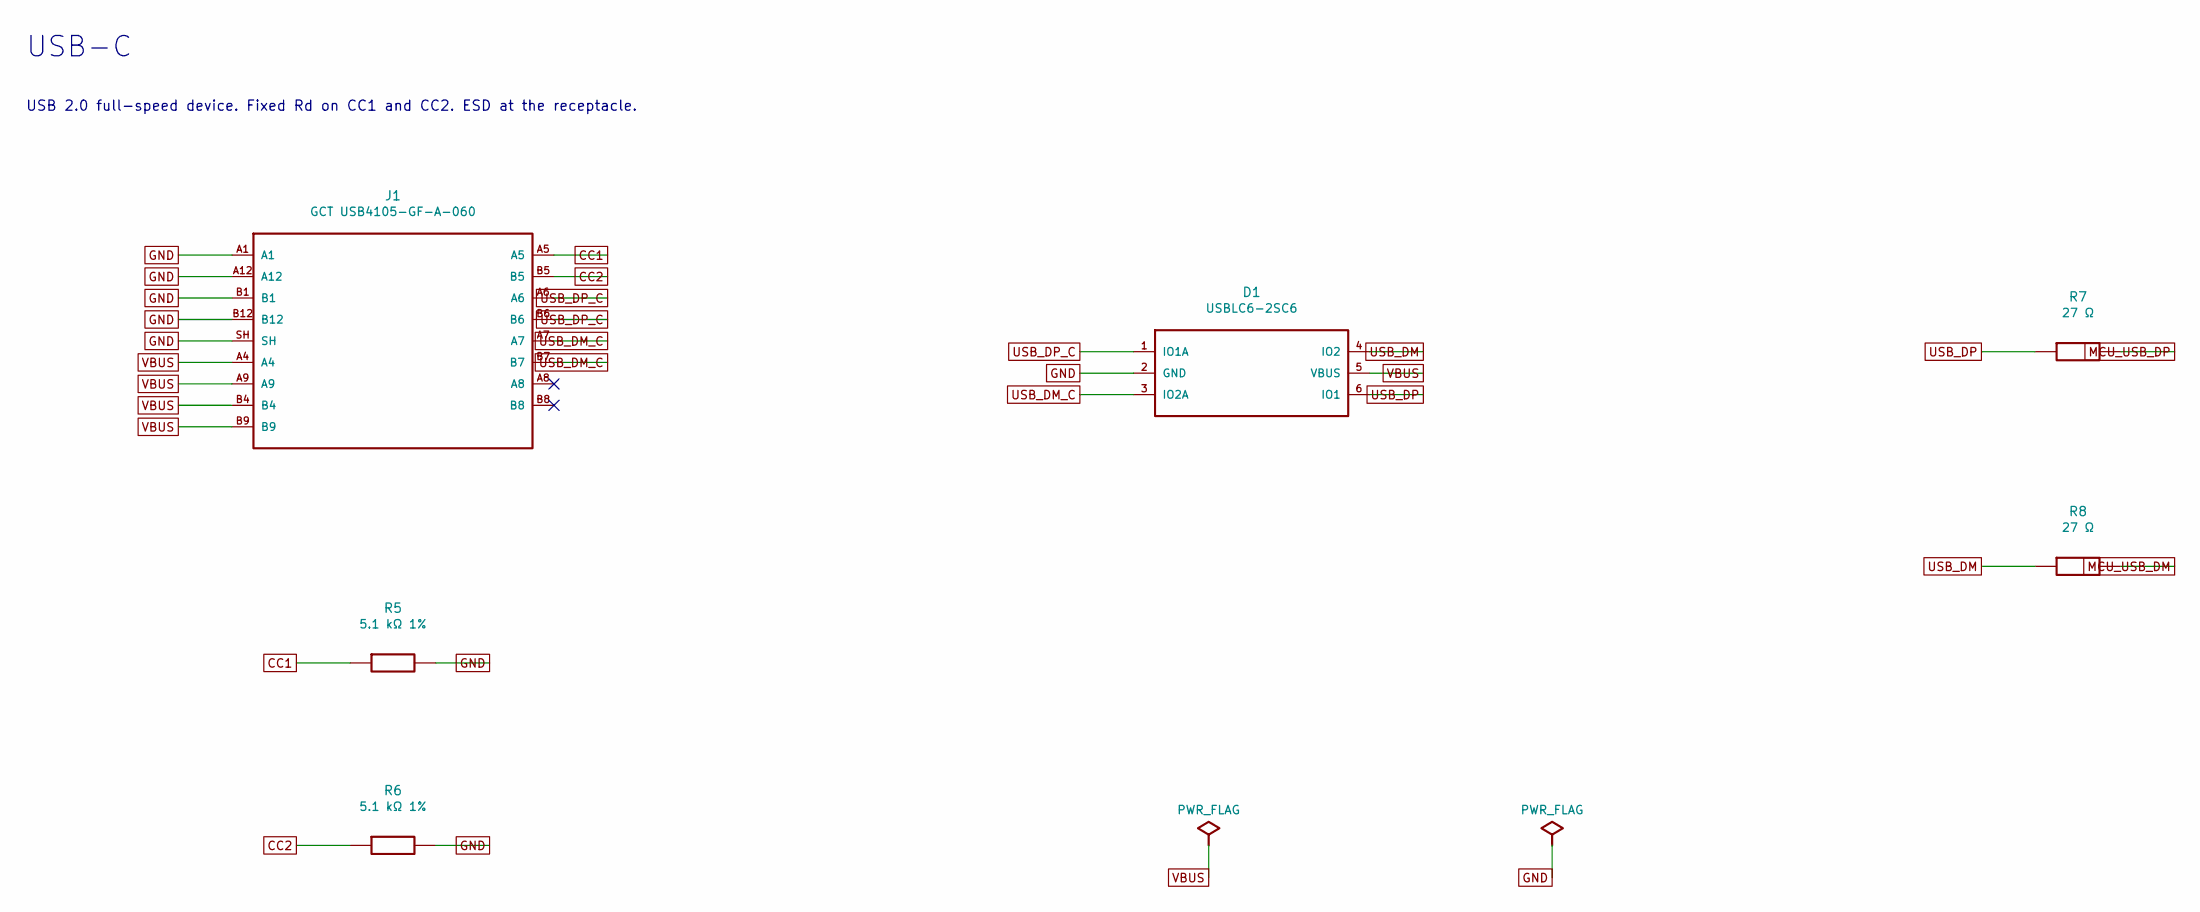
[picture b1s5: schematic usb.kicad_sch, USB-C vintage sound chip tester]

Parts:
D1: USBLC6-2SC6; SOT23_6_R90
J1: GCT USB4105-GF-A-060; USB4105
R5, R6: 5.1 kΩ 1%; R_0805_R90
R7, R8: 27 Ω; R_0402_R90

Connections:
CC1: J1.A5, R5.1
CC2: J1.B5, R6.1
GND: D1.2 (GND), J1.A1, J1.A12, J1.B1, J1.B12, J1.SH, R5.2, R6.2; also elsewhere on the board
MCU_USB_DM: R8.2; also elsewhere on the board
MCU_USB_DP: R7.2; also elsewhere on the board
USB_DM: D1.4 (IO2), R8.1
USB_DM_C: D1.3 (IO2A), J1.A7, J1.B7
USB_DP: D1.6 (IO1), R7.1
USB_DP_C: D1.1 (IO1A), J1.A6, J1.B6
VBUS: D1.5 (VBUS), J1.A4, J1.A9, J1.B4, J1.B9; also elsewhere on the board

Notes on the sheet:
USB-C
USB 2.0 full-speed device. Fixed Rd on CC1 and CC2. ESD at the receptacle.
